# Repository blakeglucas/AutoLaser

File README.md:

# Auto Laser

An automatic laser pointer mover for your cat!

## Folders

### 3D

This folder contains the STL files for 3D printing and the FreeCAD source files for easy modification. Not every FreeCAD file has an associated STL because some are used as building blocks rather than as separate parts.

### Firmware

This folder contains the MicroPython firmware. This project was initially designed for the Pi Pico W, and the BaseMount part includes a corresponding mount, but you could modify it for use with another MicroPython compatible board (or just write your own firmware).

### PCB

This folder contains the design files for a Pi Pico (W) hat that makes connecting the laser and motors to the Pi Pico much easier. This part is not required.

## BOM

| Quantity      | Part        |
| --------------| ----------- |
| 2             | TowerPro SG-5010 (or body-compatible) servo motors    |
| 1     | Pi Pico W |
| 4     | M3x8 bolts    |
| 4     | M3 nuts   |
| 5     | M2x8 bolts    |
| 5     | M2 nuts   |
| 1     | Laser diode module        |
| 2     | Longer wires for the laser module |
| 1     | Micro-USB cable and wall plug |
| Any     | Cat |

> Servos: https://www.adafruit.com/product/155

> Laser Diodes: https://www.amazon.com/gp/product/B088PQQ9XV/

## Instructions

> If using a Pi Pico (W), be sure to flash MicroPython before starting. https://micropython.org/download/rp2-pico/

1. 3D print the STL files in the `3D` folder. Print plenty of extras of `ServoShaft` and `LaserArm`.
1. Connect your Pi Pico (W) to your computer and copy the Python files in the `Firmware` folder to your board, either via [Thonny](https://thonny.org/), [mpremote](https://docs.micropython.org/en/latest/reference/mpremote.html), or another way if you know one. After copying the files, disconnect your board from the computer.
1. (If using the PicoHat PCB) Solder the PicoHat to your Pi Pico (W).
1. Disassemble your servos and replace each drive shaft with the printed `ServoShaft` piece. It should be a drop-in replacement. Reassemble.
1. Attach the Pi Pico (W) to the `BaseMount` part using four of the M2 bolts and nuts. If you're using the PicoHat PCB, it's tricky to get the two by the micro-USB port, but it is doable.
1. Attach one of the servos to the `BaseMount` part using the M3 bolts and nuts.
1. (If necessary) De-solder the stock wires from the module and solder on two longer wires.
1. Snap the laser diode module into the `LaserHolder` part.
1. Attach the `LaserHolder` part to the `LaserArm` part using the remaining M2 bolt and nut.
1. Slide the `LaserArm` part onto the free servo's shaft at as close to a 90 degree angle as you can get.
1. Insert the free servo with the `LaserArm` attached into the `YMount` part.
1. Attach the now-assembled `YMount` part to `BaseMount`.
1. Slide the servo and laser wires through the slit on the back of `BaseMount` and attach them to your Pi Pico (W), either via the provided PicoHat or another method.
1. Connect your board to a power source. The servos will be driven to the zero position (50% duty), pause for five seconds, then begin the random laser movement.

## 3D Printing Instructions

> If you haven't tried the "Lightning" fill pattern in PrusaSlicer/SuperSlicer, give it a shot.

### BaseMount

Print top-face-down, using supports for only the counterbore screw holes on the face. Any infill, any layer height (0.2mm recommended).

### LaserArm

Print with the gear attachment hole facing up. Use support for only the counterbore screw hole. Sparse infill is fine, any layer height (18% and 0.2mm recommended, respectively).

### LaserHolder

Print the obvious orientation. No supports required. A finer layer height could be beneficial, but 0.2mm will work just fine.

### ServoShaft

If you have a printer with a 0.2-0.25mm nozzle, that is preferable, but a 0.4mm nozzle will work too. Add a support enforcer for the large negative area inside the gear, but support is not required for inside the smaller hole. 0.2mm layer height recommended, 100% infill for strength.

### YMount

Print the obvious orientation. Use support for the inset hole but not for inside the gear hole. Sparse infill, 0.2mm layer height recommended.

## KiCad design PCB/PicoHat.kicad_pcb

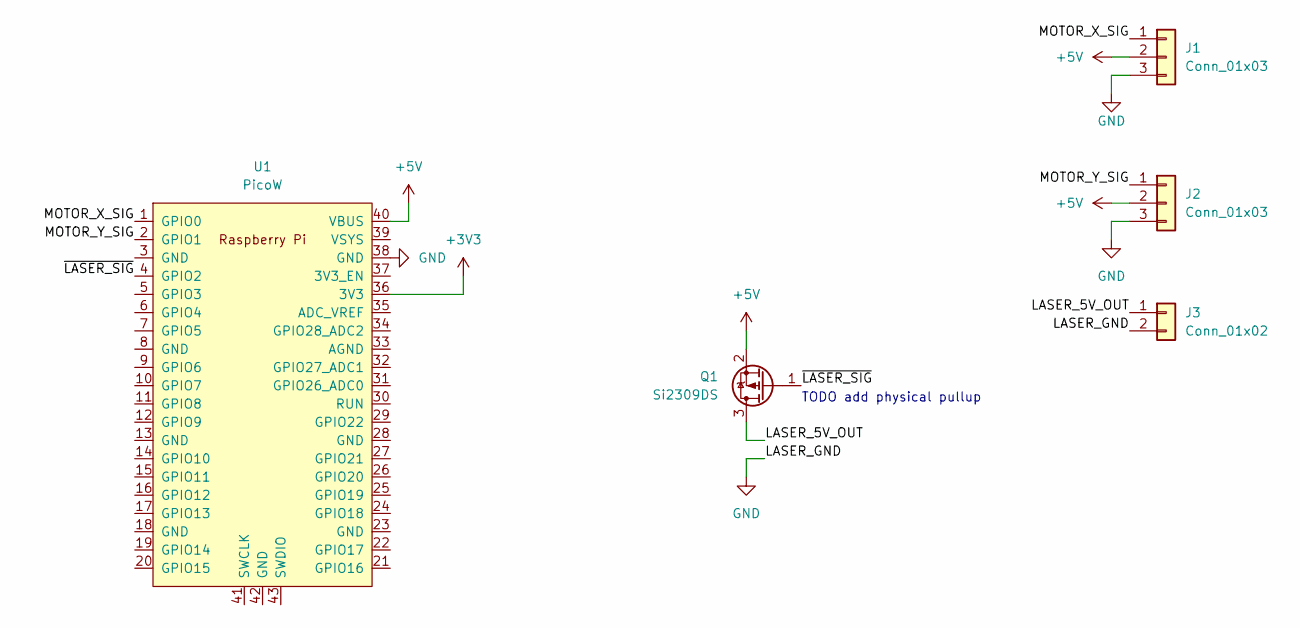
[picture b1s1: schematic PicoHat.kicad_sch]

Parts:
J1, J2: Conn_01x03; PinHeader_1x03_P2.54mm_Vertical
J3: Conn_01x02; PinSocket_1x02_P2.00mm_Vertical
Q1: Si2309DS; SOT-23
U1: PicoW; RPi_PicoW_SMD_TH

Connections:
+3V3: U1.36 (3V3)
+5V: J1.2, J2.2, Q1.2 (S), U1.40 (VBUS)
/LASER_5V_OUT: J3.1, Q1.3 (D)
/MOTOR_X_SIG: J1.1, U1.1 (GPIO0)
/MOTOR_Y_SIG: J2.1, U1.2 (GPIO1)
/~LASER_SIG: Q1.1 (G), U1.4 (GPIO2)
GND: J1.3, J2.3, J3.2, U1.38 (GND)

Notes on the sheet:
TODO add physical pullup

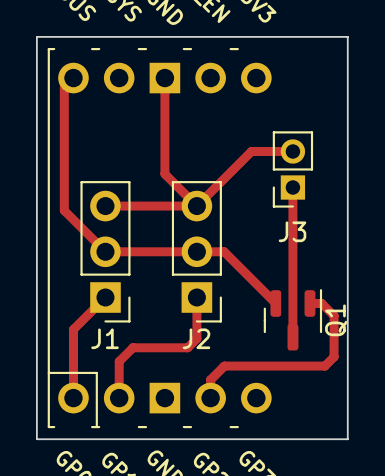
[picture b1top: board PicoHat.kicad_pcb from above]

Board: 2 copper layers, 17.3 x 22.4 mm, 5 parts (0 on the bottom side), 6 nets.

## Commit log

2023-03-27 Intial commit
2023-03-27 Added images
2023-03-27 Added image to README
2023-03-27 ServoShaft v2, removed instant snap to home in ServoDriver
2023-03-27 Using defined ranges in randrange to keep Y from being constantly at min
2023-03-27 Added gcode files to gitignore
